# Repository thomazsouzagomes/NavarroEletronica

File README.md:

# NavarroEletronica

Os arquivos aqui são utilizados nas vídeo aulas do canal Navarro Eletrônica no Youtube.
A intenção é ensinar Arduino de uma forma completamente diferente.

http://www.youtube.com/c/NavarroEletrônica
www.navarroeletronica.com

Todo o material aqui é FREE TO USE, na faixa, 0800 ou como preferir.

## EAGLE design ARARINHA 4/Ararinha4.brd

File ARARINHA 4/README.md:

# NavarroEletronica

PCB para o projeto ARARINHA 4 de Miguel PY2OHH

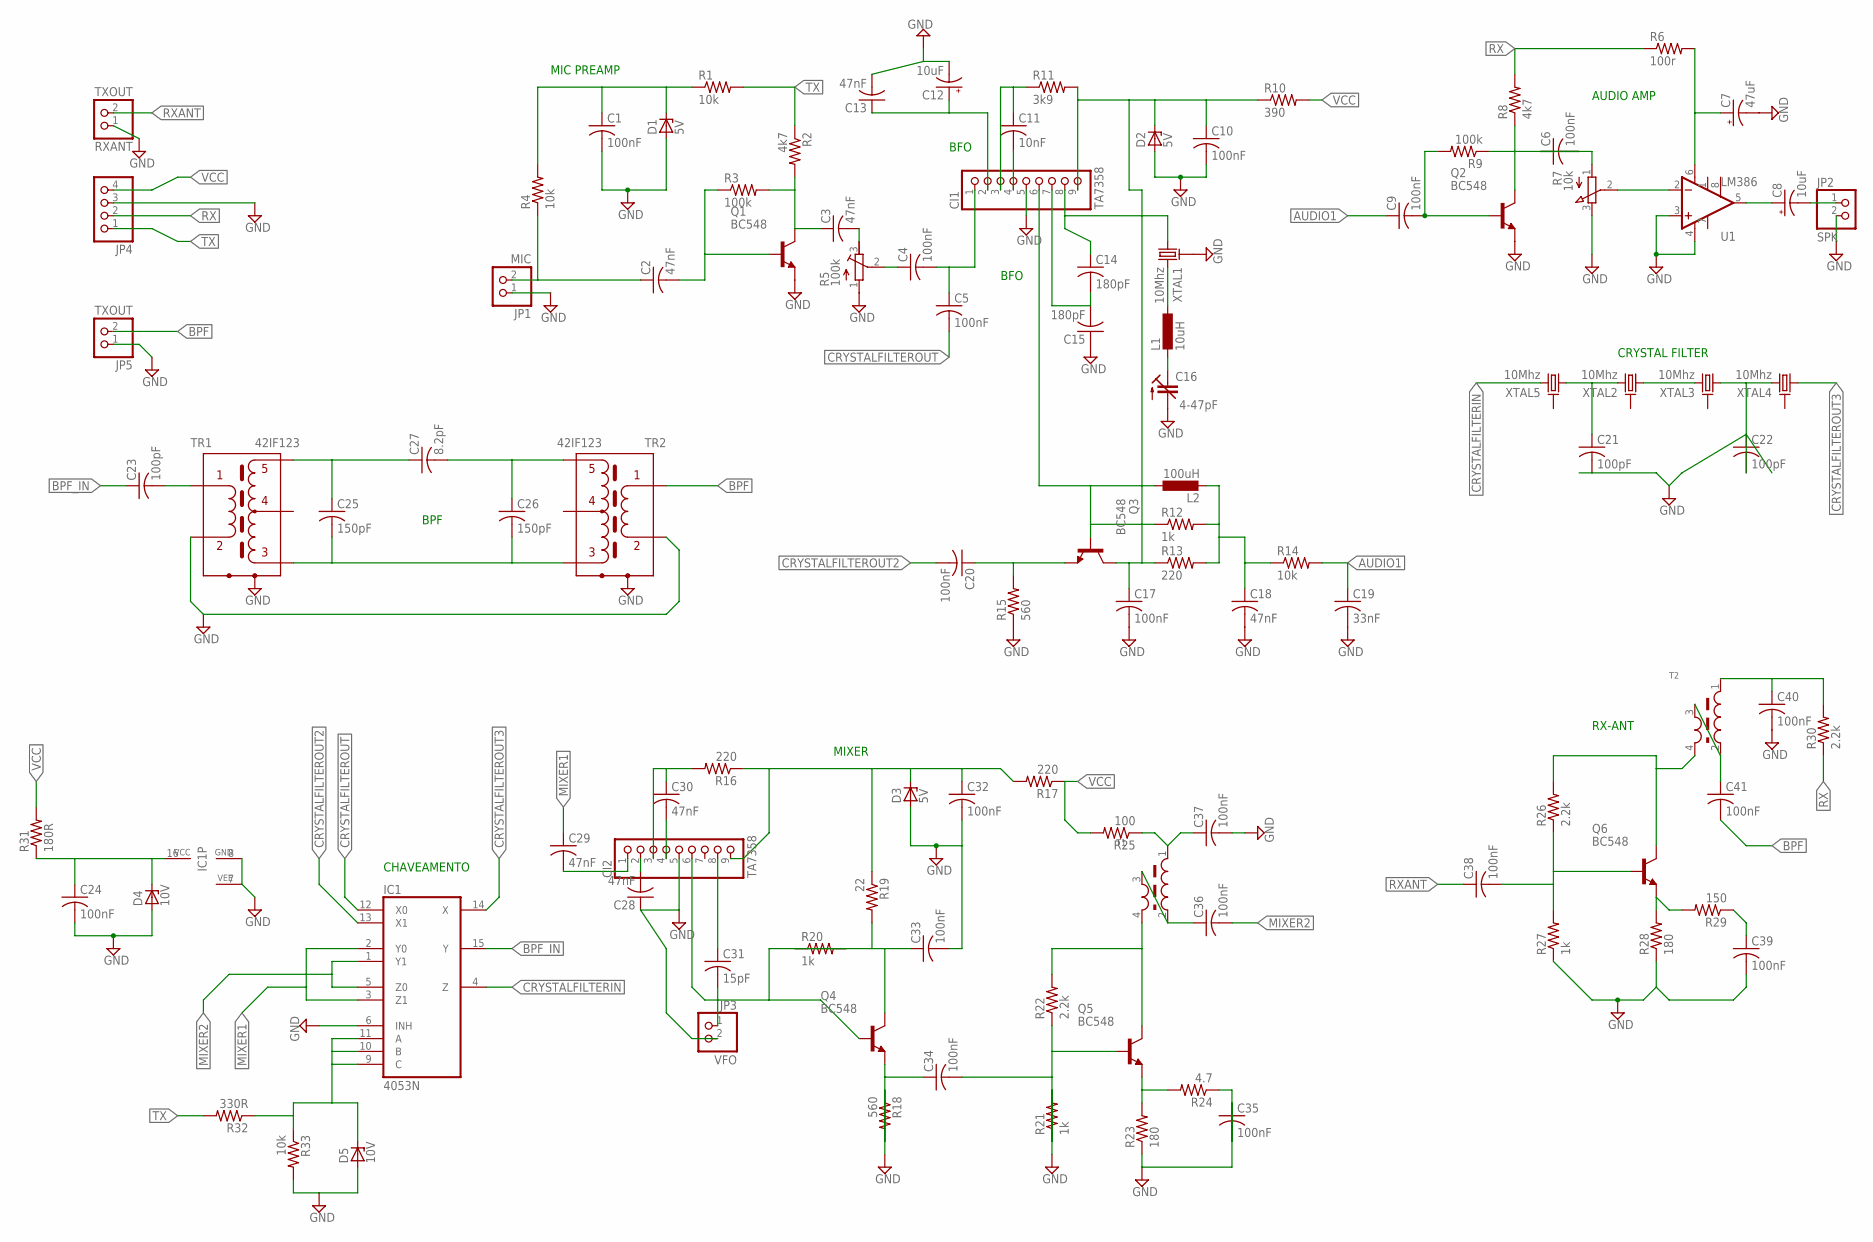
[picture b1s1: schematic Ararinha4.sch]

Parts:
C1, C4, C5, C6, C9, C10, C17, C20, C24, C32, C33, C34, C35, C36, C37, C38, C39, C40, C41: 100nF; C050-030X075
C2, C3, C13, C18, C28, C29, C30: 47nF; C050-030X075
C7: 47uF; E5-6
C8, C12: 10uF; E5-6
C11: 10nF; C050-030X075
C14, C15: 180pF; C050-030X075
C16: 4-47pF; CTRIM3050.504
C19: 33nF; C050-030X075
C21, C22, C23: 100pF; C050-030X075
C25, C26: 150pF; C050-030X075
C27: 8.2pF; C050-030X075
C31: 15pF; C050-030X075
CI1, CI2: TA7358; 1X09
D1, D2, D3: 5V; ZDIO-5
D4, D5: 10V; ZDIO-5
IC1: 4053N; DIL16
JP1: MIC; 1X02
JP2: SPK; 1X02
JP3: VFO; 1X02
JP4: PINHD-1X4; 1X04
JP5: TXOUT; 1X02
L1: 10uH; 0207/7
L2: 100uH; 0207/7
Q1, Q2, Q3, Q4, Q5, Q6: BC548; TO92-EBC
R1, R4, R14, R33: 10k; 0204/7
R2, R8: 4k7; 0204/7
R3, R9: 100k; 0204/7
R5: 100k; RTRIM3299W
R6: 100r; 0204/7
R7: 10k; 3RP/1610N
R10: 390; 0204/7
R11: 3k9; 0204/7
R12, R20, R21, R27: 1k; 0204/7
R13, R16, R17: 220; 0204/7
R15, R18: 560; 0204/7
R19: 22; 0204/7
R22, R26, R30: 2.2k; 0204/7
R23, R28: 180; 0204/7
R24: 4.7; 0204/7
R25: 100; 0204/7
R29: 150; 0204/7
R31: 180R; 0204/7
R32: 330R; 0204/7
RXANT: TXOUT; 1X02
T1, T2: TOROID-T37-4PIN
TR1, TR2: 42IF123
U1: LM386; DIP08
XTAL1, XTAL2, XTAL3, XTAL4, XTAL5: 10Mhz; CRISTAL_EM_PÉ

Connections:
AUDIO1: C9.1, C19.1, R14.2
BPF: C41.2, JP5.2, TR2.P$1 (1)
BPF_IN: C23.1, IC1.15 (Y)
CRYSTALFILTERIN: IC1.4 (Z), XTAL5.1 (2)
CRYSTALFILTEROUT: C5.2, IC1.12 (X0)
CRYSTALFILTEROUT2: C20.2, IC1.13 (X1)
CRYSTALFILTEROUT3: IC1.14 (X), XTAL4.2 (1)
GND: C1.2, C7.-, C10.2, C12.-, C13.2, C15.1, C16.2 (A), C17.2, C18.2, C19.2, C21.2, C22.1, C24.2, C28.1, C32.2, C33.2, C35.1, C37.2, C39.2, C40.2, CI1.5, CI2.5, D1.A, D2.A, D3.A, D4.A, D5.A, IC1.6 (INH), IC1.7 (VEE), IC1.8 (GND), JP1.1, JP2.2, JP3.2, JP4.3, JP5.1, Q1.E, Q2.E, R5.1 (E), R7.3 (E), R15.1, R18.1, R21.2, R23.1, R27.1, R28.1, R33.2, RXANT.1, TR1.P$2 (2), TR1.P$7 (7), TR2.P$2 (2), TR2.P$6 (6), U1.3 (+IN), U1.4 (V-), XTAL1.GND
MIXER1: C29.1, IC1.2 (Y0), IC1.3 (Z1)
MIXER2: C36.2, IC1.1 (Y1), IC1.5 (Z0)
unnamed: C1.1, D1.C, R1.1, R4.2
unnamed: C3.2, R5.3 (A)
unnamed: C4.1, R5.2 (S)
unnamed: C4.2, C5.1, CI1.1
unnamed: C3.1, Q1.C, R2.2, R3.2
unnamed: C2.2, Q1.B, R3.1
unnamed: C2.1, JP1.2, R4.1
unnamed: C9.2, Q2.B, R9.2
unnamed: C7.+, R6.2, U1.6 (V+)
unnamed: C6.1, R7.1 (A)
unnamed: C8.+, U1.5 (OUT)
unnamed: C8.-, JP2.1
unnamed: R7.2 (S), U1.2 (-IN)
unnamed: C6.2, Q2.C, R8.1, R9.1
unnamed: C20.1, Q3.E, R15.2
unnamed: C11.2, CI1.4
unnamed: C11.1, CI1.3, R11.1
unnamed: L1.1, XTAL1.1 (2)
unnamed: C12.+, C13.1, CI1.2
unnamed: C16.1 (E), L1.2
unnamed: C14.2, C15.2, CI1.7
unnamed: C14.1, CI1.8, XTAL1.2 (1)
unnamed: CI1.6, L2.1, Q3.B, R12.1
unnamed: C10.1, C17.1, CI1.9, D2.C, Q3.C, R10.1, R11.2, R13.1
unnamed: C21.1, XTAL2.1 (2), XTAL5.2 (1)
unnamed: C18.1, L2.2, R12.2, R13.2, R14.1
unnamed: XTAL2.2 (1), XTAL3.1 (2)
unnamed: C22.2, XTAL3.2 (1), XTAL4.1 (2)
unnamed: C25.2, C26.2, TR1.P$3 (3), TR2.P$3 (3)
unnamed: C28.2, CI2.2
unnamed: C23.2, TR1.P$1 (1)
unnamed: D5.C, IC1.9 (C), IC1.10 (B), IC1.11 (A), R32.1, R33.1
unnamed: C26.1, C27.2, TR2.P$5 (5)
unnamed: C25.1, C27.1, TR1.P$5 (5)
unnamed: C29.2, CI2.1
unnamed: C30.2, CI2.4
unnamed: C30.1, CI2.3, R16.2
unnamed: C32.1, CI2.9, D3.C, R16.1, R17.2, R19.1
unnamed: C31.1, CI2.8
unnamed: C31.2, JP3.1
unnamed: C34.1, Q4.E, R18.2
unnamed: CI2.6, Q4.B, R20.2
unnamed: C35.2, R24.1
unnamed: C33.1, Q4.C, R19.2, R20.1
unnamed: C36.1, T1.2, T1.3
unnamed: C34.2, Q5.B, R21.1, R22.1
unnamed: Q5.C, R22.2, T1.4
unnamed: Q5.E, R23.2, R24.2
unnamed: C37.1, R25.1, T1.1
unnamed: C38.2, Q6.B, R26.1, R27.2
unnamed: Q6.E, R28.2, R29.2
unnamed: C39.1, R29.1
unnamed: C24.1, D4.C, IC1.16 (VCC), R31.1
unnamed: Q6.C, R26.2, T2.4
unnamed: C41.1, T2.2, T2.3
unnamed: C40.1, R30.2, T2.1
RX: JP4.2, R6.1, R8.2, R30.1
RXANT: C38.1, RXANT.2
TX: JP4.1, R1.2, R2.1, R32.2
VCC: JP4.4, R10.2, R17.1, R25.2, R31.2

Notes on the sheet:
MIC PREAMP
BFO
CRYSTAL FILTER
MIXER
CHAVEAMENTO
RX-ANT
AUDIO AMP
BPF

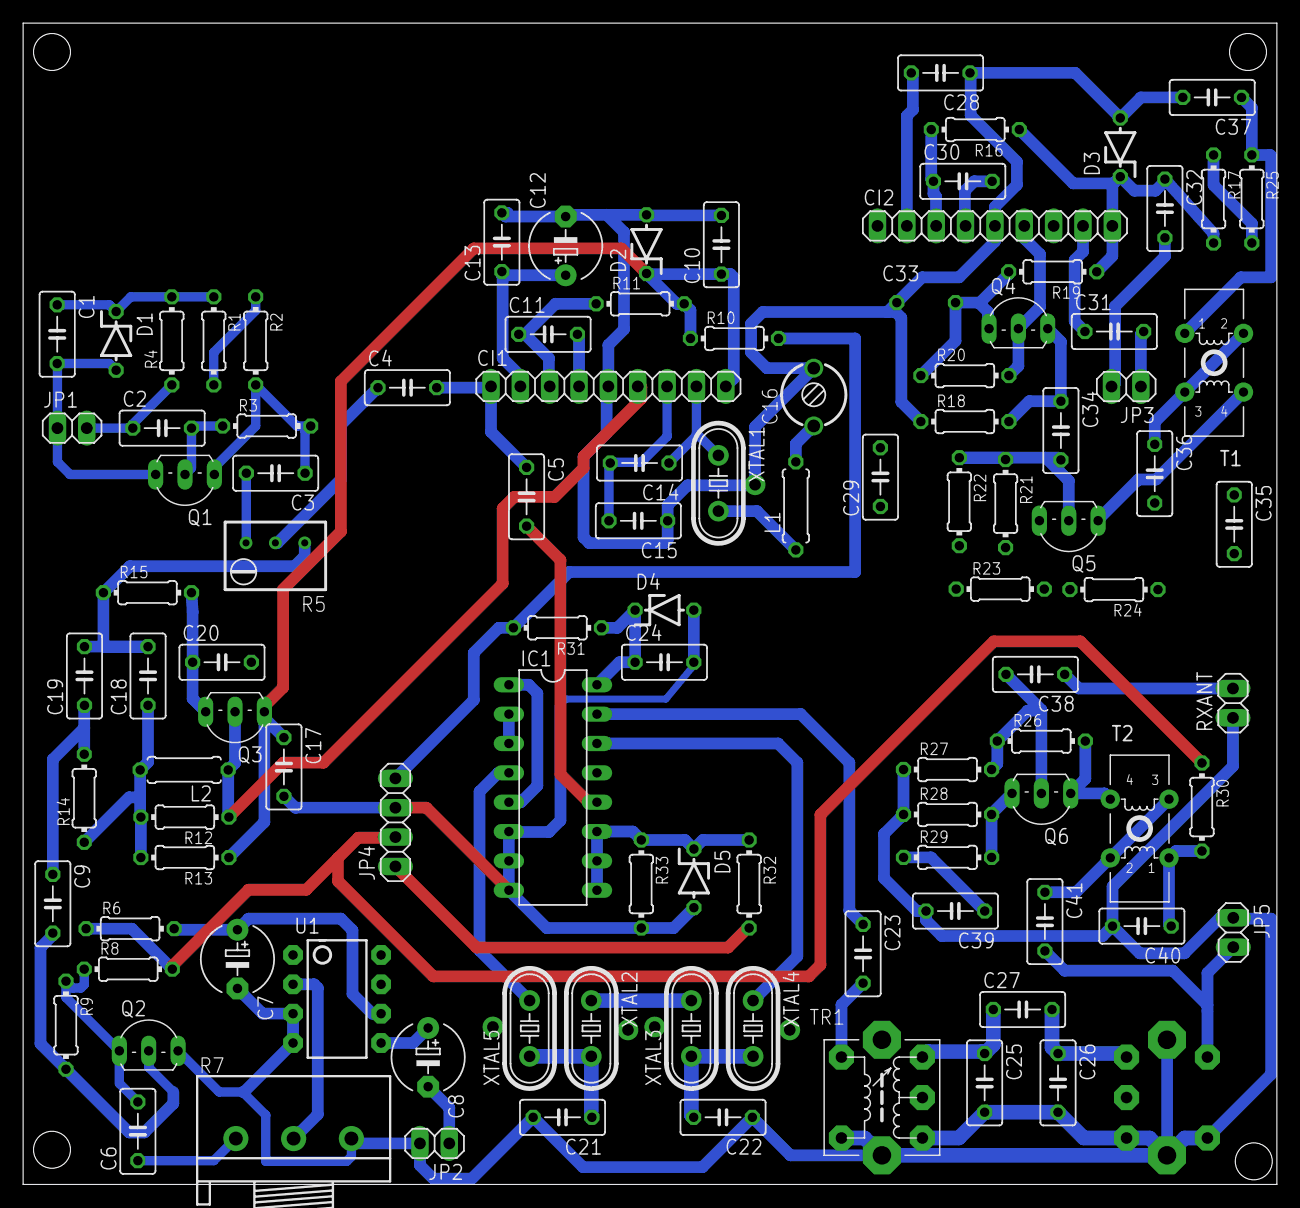
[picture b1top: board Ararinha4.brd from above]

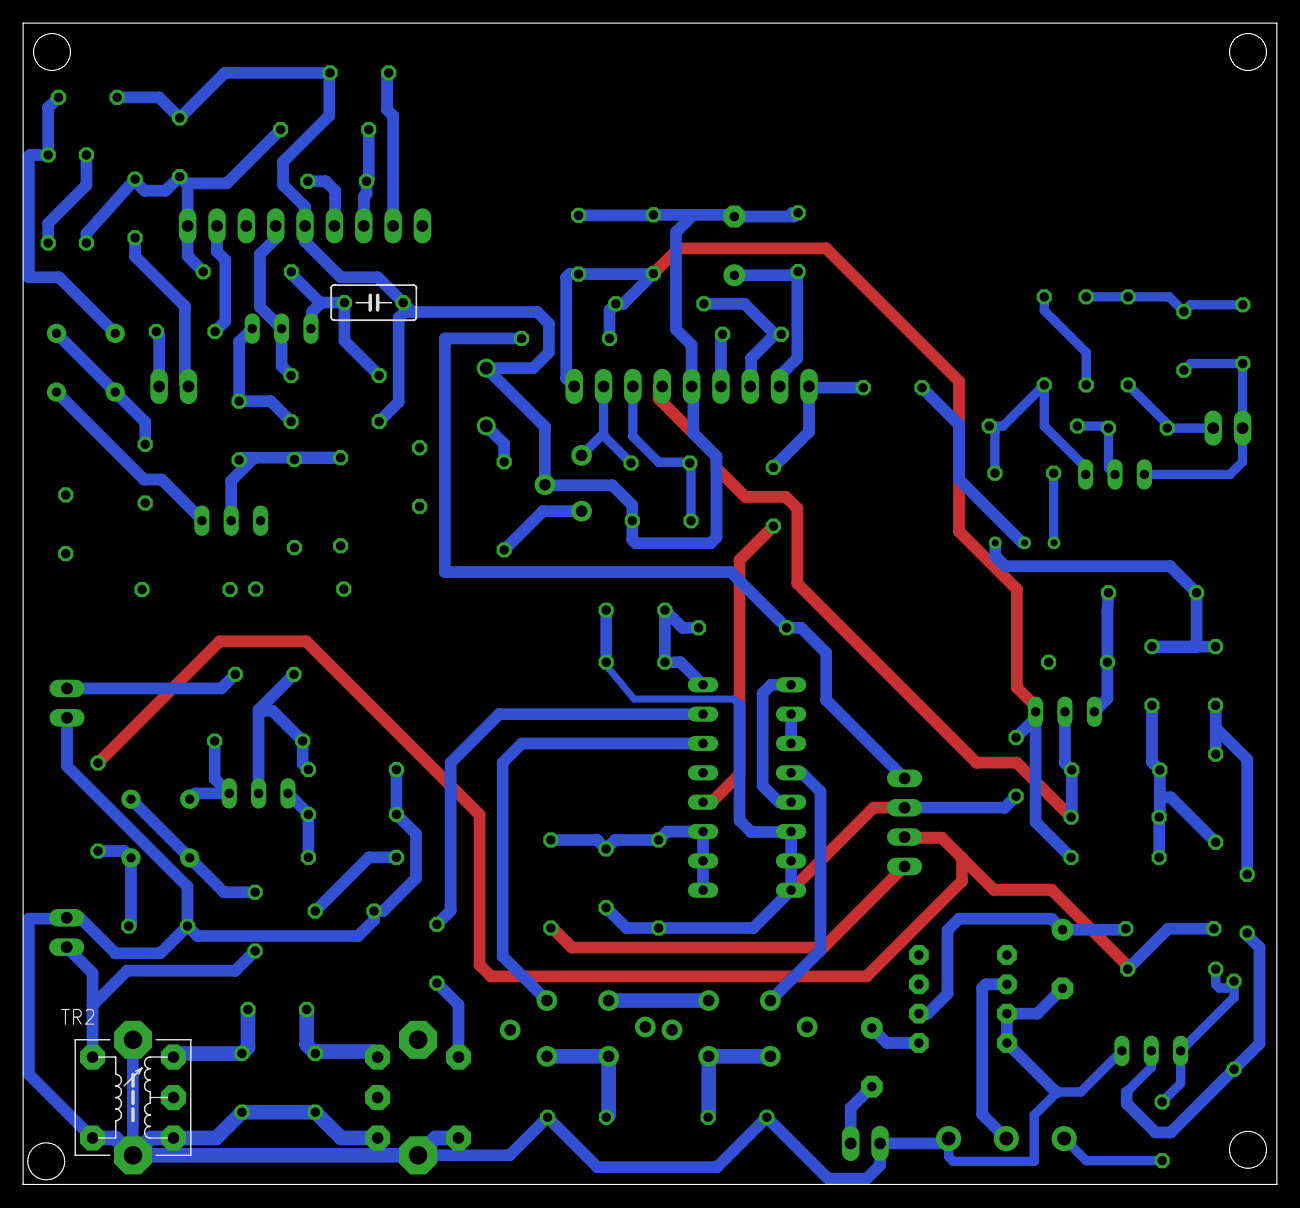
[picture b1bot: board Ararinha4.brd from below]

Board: 2 copper layers, 108.5 x 100.5 mm, 106 parts (2 on the bottom side), 70 nets.

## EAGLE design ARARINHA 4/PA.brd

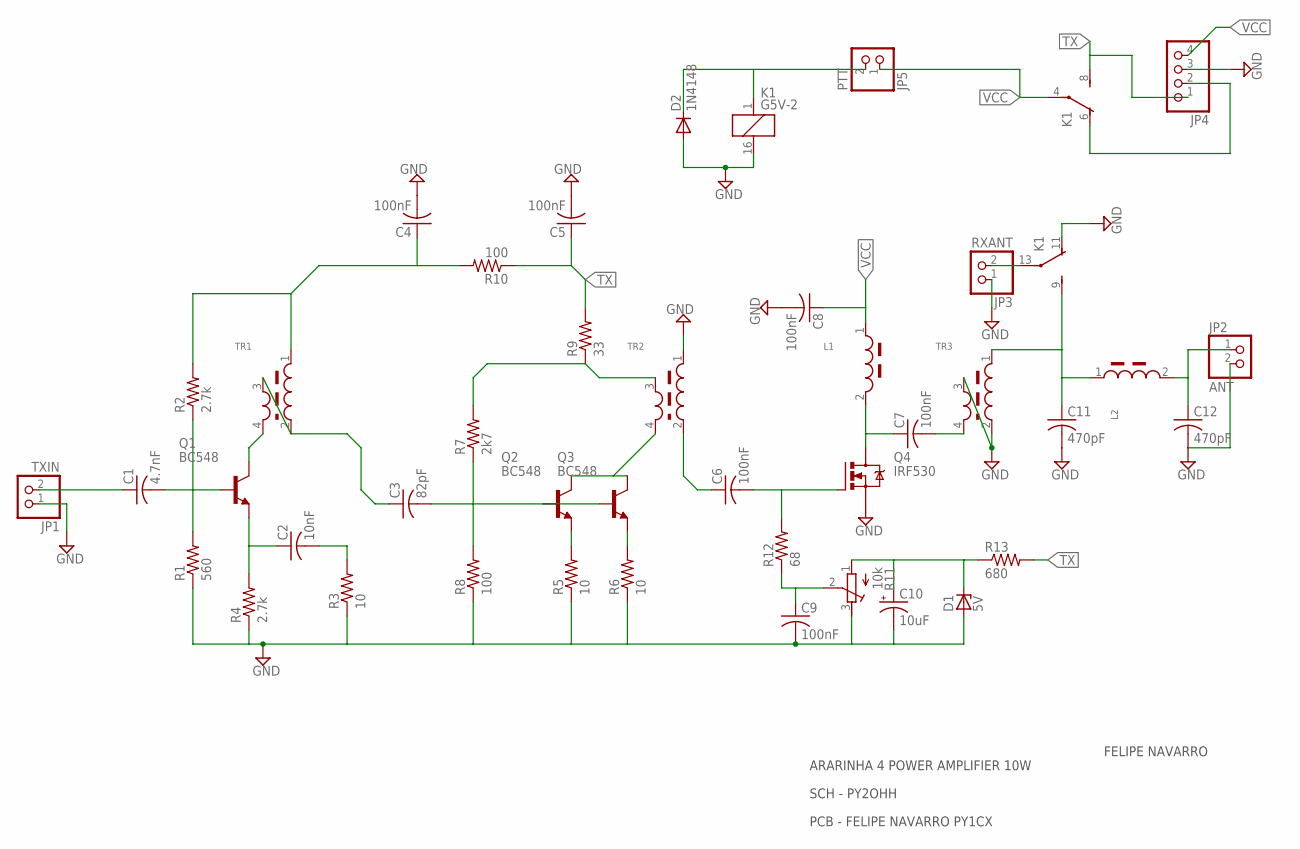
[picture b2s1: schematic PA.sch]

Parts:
C1: 4.7nF; C050-030X075
C2: 10nF; C050-030X075
C3: 82pF; C050-030X075
C4, C5, C6, C7, C8, C9: 100nF; C050-030X075
C10: 10uF; E3,5-8
C11, C12: 470pF; C050-030X075
D1: 5V; DO35Z10
D2: 1N4148; DO35-7
JP1: TXIN; 1X02
JP2: ANT; 1X02
JP3: RXANT; 1X02
JP4: PINHD-1X4; 1X04
JP5: PTT; 1X02
K1: G5V-2
L1, L2: TOROID-T37-2PIN
Q1, Q2, Q3: BC548; TO92-EBC
Q4: IRF530; TO220BV
R1: 560; 0204/7
R2, R4: 2.7k; 0204/7
R3, R5, R6: 10; 0204/7
R7: 2k7; 0204/7
R8, R10: 100; 0204/7
R9: 33; 0204/7
R11: 10k; RTRIM64W
R12: 68; 0204/7
R13: 680; 0204/7
TR1, TR2, TR3: TOROID-T37-4PIN

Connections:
GND: C4.2, C5.2, C8.2, C9.2, C10.-, C11.2, C12.2, D1.A, D2.A, JP1.1, JP2.2, JP3.1, JP4.3, K1.11 (O), K1.16 (2), Q4.S, R1.1, R3.1, R4.1, R5.1, R6.1, R8.1, R11.3 (A), TR2.1, TR3.2, TR3.3
unnamed: C1.2, Q1.B, R1.2, R2.1
unnamed: C2.2, R3.2
unnamed: C4.1, R2.2, R10.2, TR1.1
unnamed: C1.1, JP1.2
unnamed: C2.1, Q1.E, R4.2
unnamed: C3.1, TR1.2, TR1.3
unnamed: Q1.C, TR1.4
unnamed: Q2.E, R5.2
unnamed: Q3.E, R6.2
unnamed: Q2.C, Q3.C, TR2.4
unnamed: R7.2, R9.1, TR2.3
unnamed: C3.2, Q2.B, Q3.B, R7.1, R8.2
unnamed: C9.1, R11.2 (S), R12.1
unnamed: C10.+, D1.C, R11.1 (E), R13.1
unnamed: JP3.2, K1.13
unnamed: C6.1, TR2.2
unnamed: C6.2, Q4.G, R12.2
unnamed: C7.1, L1.2, Q4.D
unnamed: C7.2, TR3.4
unnamed: C12.1, JP2.1, L2.2
unnamed: C11.1, K1.9 (S), L2.1, TR3.1
unnamed: JP4.2, K1.6 (O)
unnamed: D2.C, JP5.2, K1.1
TX: C5.1, JP4.1, K1.8 (S), R9.2, R10.1, R13.2
VCC: C8.1, JP4.4, JP5.1, K1.4, L1.1

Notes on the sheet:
PCB - FELIPE NAVARRO PY1CX
SCH - PY2OHH
ARARINHA 4 POWER AMPLIFIER 10W
FELIPE NAVARRO

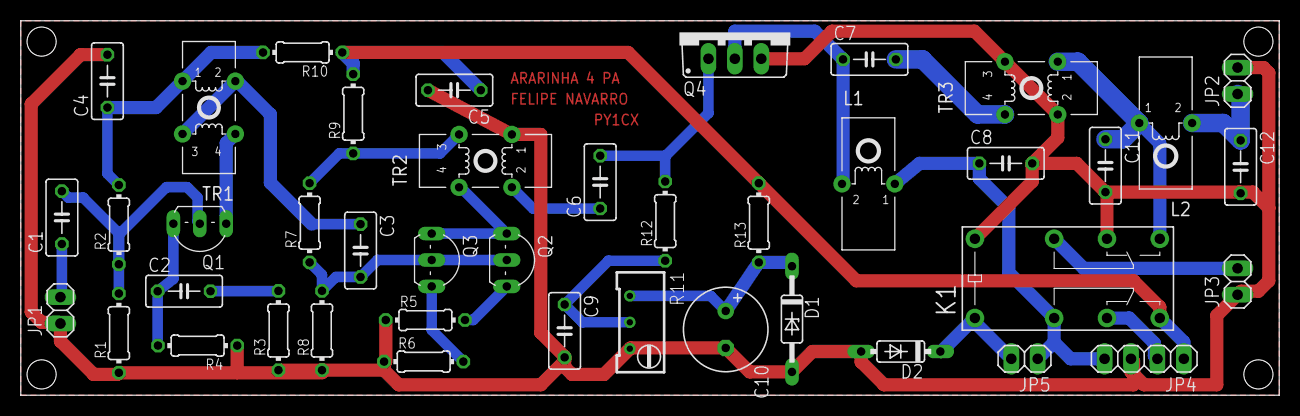
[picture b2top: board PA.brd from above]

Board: 2 copper layers, 121.0 x 36.0 mm, 42 parts (0 on the bottom side), 26 nets.

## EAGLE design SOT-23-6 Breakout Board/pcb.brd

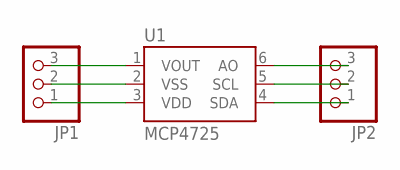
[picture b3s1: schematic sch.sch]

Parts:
JP1, JP2: PINHD-1X3; 1X03
U1: MCP4725; SOT23-6

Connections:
unnamed: JP1.1, U1.3 (VDD)
unnamed: JP1.2, U1.2 (VSS)
unnamed: JP1.3, U1.1 (VOUT)
unnamed: JP2.3, U1.6 (AO)
unnamed: JP2.2, U1.5 (SCL)
unnamed: JP2.1, U1.4 (SDA)

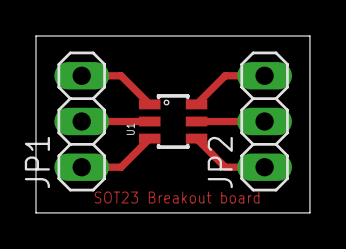
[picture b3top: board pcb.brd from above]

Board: 2 copper layers, 15.2 x 9.8 mm, 3 parts (0 on the bottom side), 6 nets.

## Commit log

2015-03-24 Alguns projetos e exemplos a serem utilizados nas aulas.
2015-03-24 Update README.md
    Comentário inicial.
2015-03-29 Atualizado com a aula 2, termostato do Sergio ainda em desenvolvimento (falta tempo)
2015-04-01 Retirado o Delay do void setup porque com a biblioteca Timerone ele não iria funcionar, tentei fazer um delay com o for porém por algum motivo extraterreno não funcionou. Ok, trabalhamos nisso amanhã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
2015-04-01 Burro! Burro! Esqueci de trocar na função void lm35_read, após o and do aquecimento a variavel como _RD, que utilizo para os valores lidos :) Boa noite!
2015-04-12 Modifiquei praticamente todo o termostato.
2015-04-22 PCB Rev1 do PA
2015-04-22 Adicionado o PA do Ararinha 4 pronto para transferência termica (ainda passível de testes); primeiras partes da mainboard do Ararinha 4 sendo desenhadas.
2015-04-22 Várias placas na mesma folha :)
2015-04-22 SOT-23-6 Breakout Board for ADS1110 or any other component with this same package.
2015-05-04 Atualizado com o ground plane do BOTTOM, ainda falta modificar os arquivos em PDF.
2015-05-18 Aula para o canal Navarro Eletrônica http://www.youtube.com/c/NavarroEletrônica

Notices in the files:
parts and their libraries:
Sparkfun-Eagle-Libraries: Licensing:Creative Commons ShareAlike 4.0 International - https://creativecommons.org/licenses/by-sa/4.0
